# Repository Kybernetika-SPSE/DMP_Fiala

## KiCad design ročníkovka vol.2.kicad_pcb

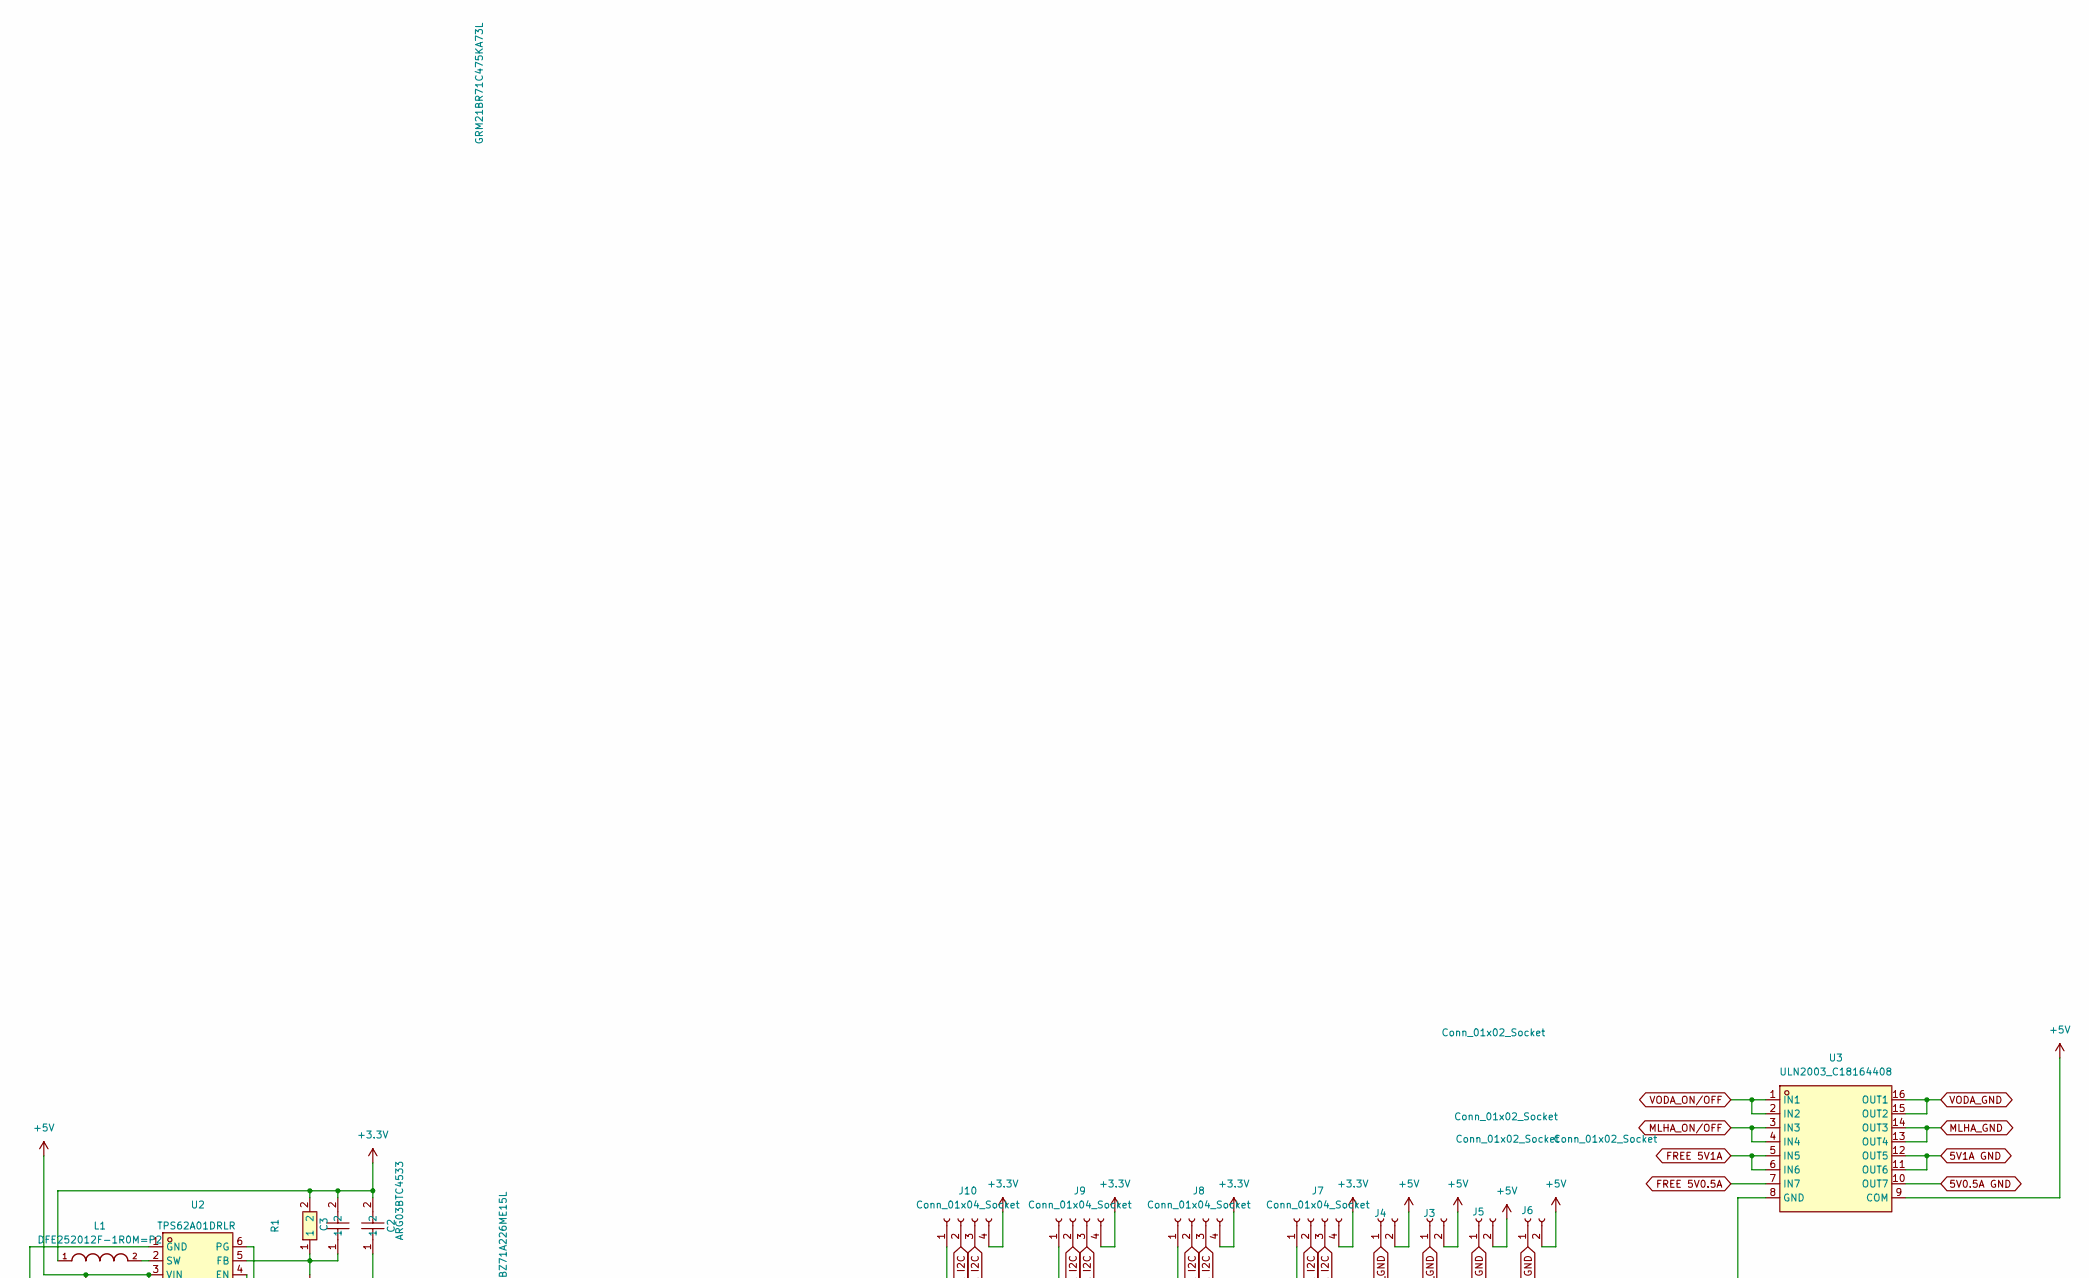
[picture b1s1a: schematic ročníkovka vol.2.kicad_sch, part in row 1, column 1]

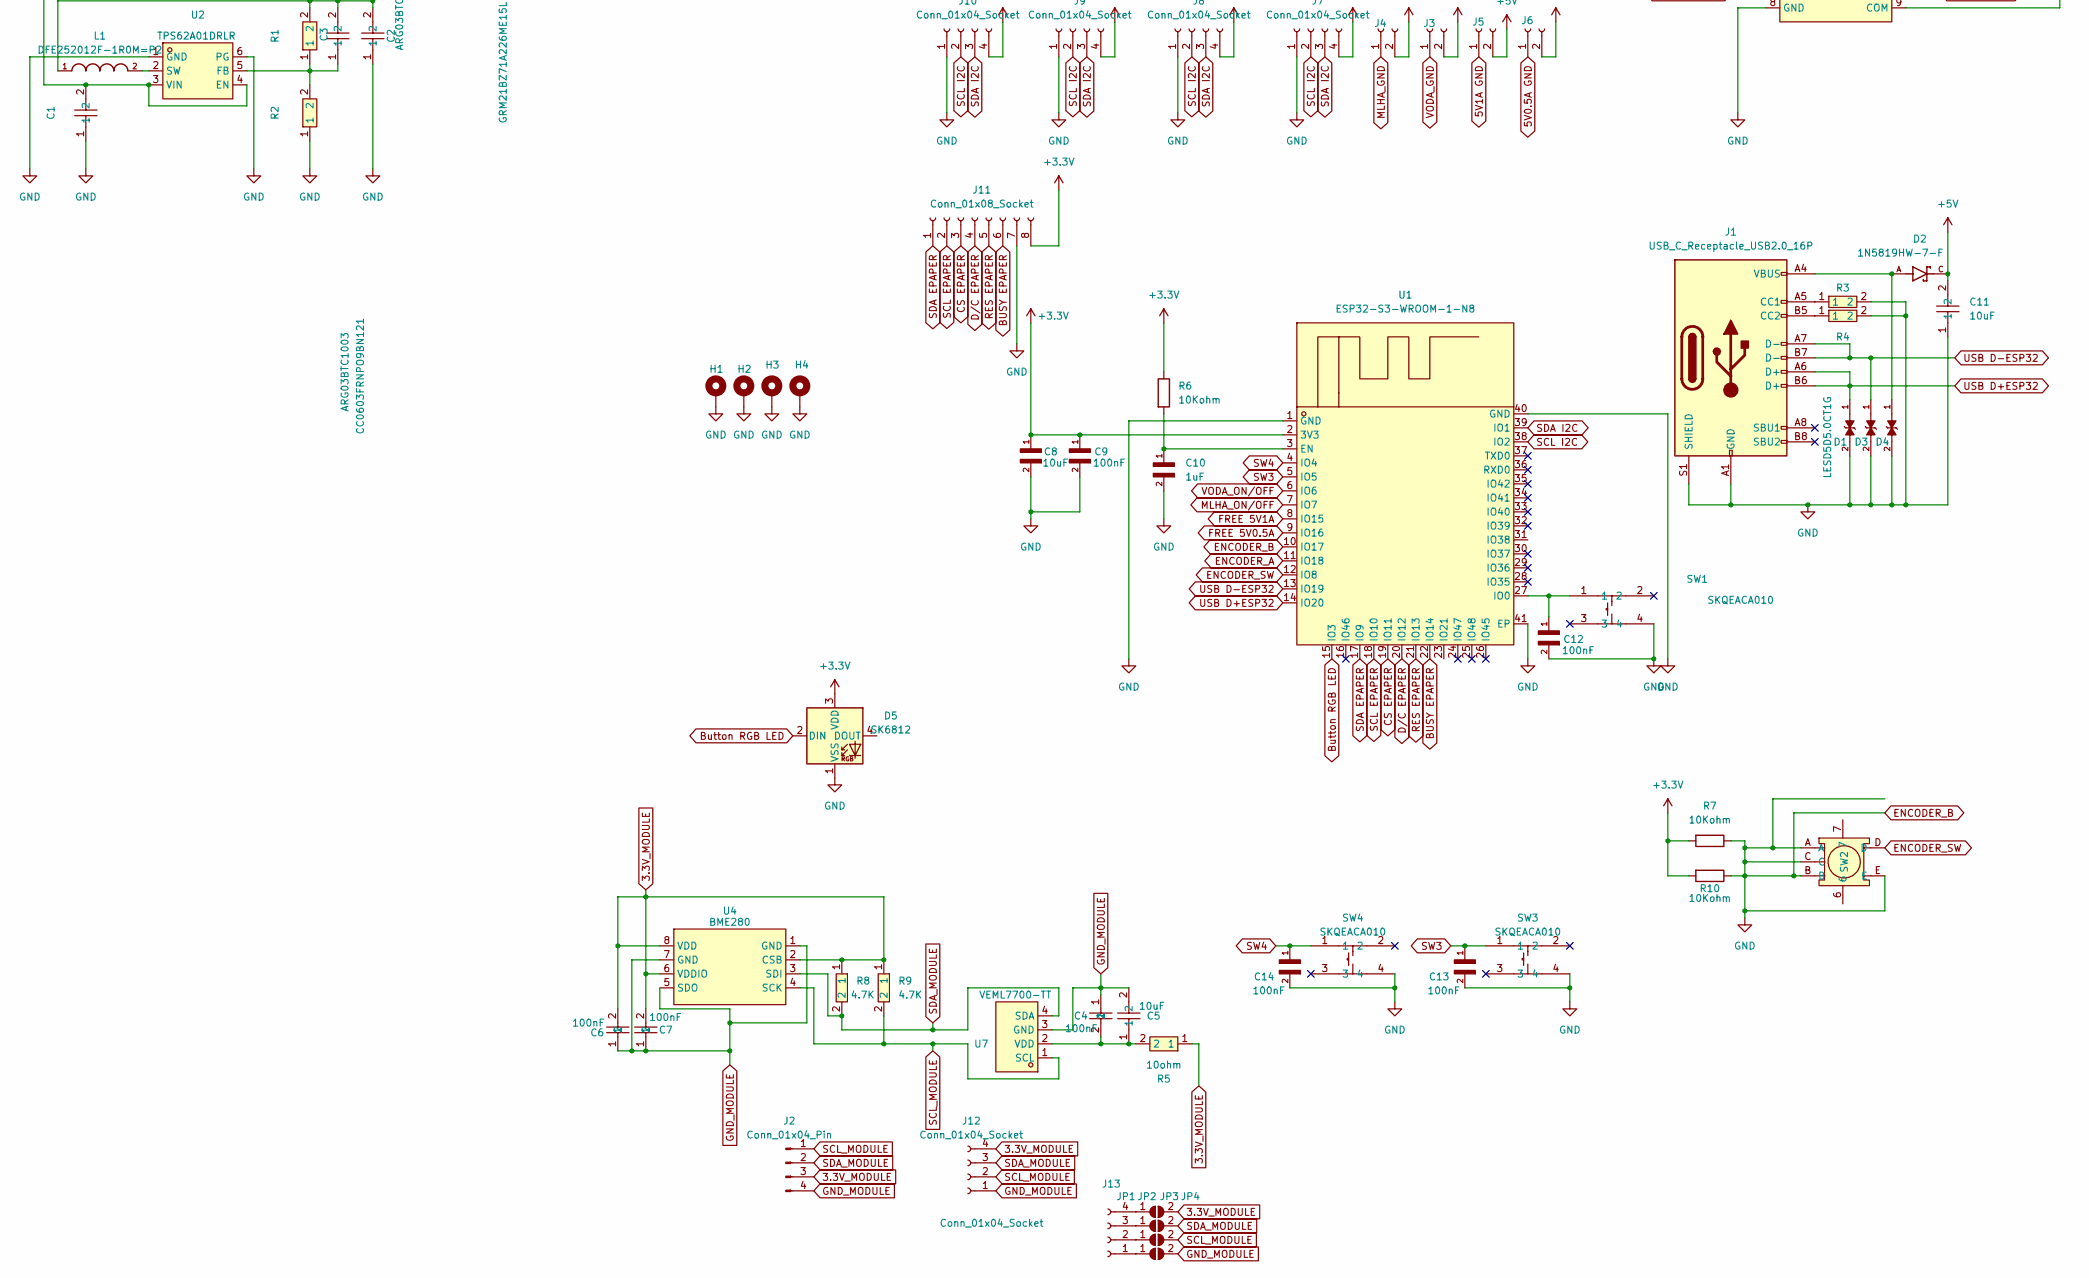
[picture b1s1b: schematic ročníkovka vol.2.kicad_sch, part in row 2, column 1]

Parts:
C1: GRM21BR71C475KA73L; C0805; LCSC Part C86040
C2: GRM21BZ71A226ME15L; C0805; LCSC Part C907991
C3: CC0603FRNPO9BN121; C0603; LCSC Part C519498
C4, C6, C7: 100nF; C0603; LCSC Part C24452
C5: 10uF; C0603; LCSC Part C962136
C8: 10uF; CAPC1608X90N
C9, C12, C13, C14: 100nF; CAPC1608X90N
C10: 1uF; CAPC1608X90N
C11: 10uF; C0603; LCSC Part C96446
D1, D3, D4: LESD5D5.0CT1G; TVS_LESD5D5.0CT1G; PARTREV O
D2: 1N5819HW-7-F; SOD3715X145N; PARTREV 18-2
D5: SK6812; LED_SK6812_PLCC4_5.0x5.0mm_P3.2mm
H1, H2, H3, H4: MountingHole_Pad; MountingHole_3.2mm_M3_Pad_TopBottom
J1: USB_C_Receptacle_USB2.0_16P; USB_C_Receptacle_GCT_USB4105-xx-A_16P_TopMnt_Horizontal; LCSC Part C2988369
J2: Conn_01x04_Pin; JST_PH_B4B-PH-K_1x04_P2.00mm_Vertical
J3, J4, J5, J6: Conn_01x02_Socket; JST_PH_S2B-PH-K_1x02_P2.00mm_Horizontal
J7, J8, J9, J10, J12, J13: Conn_01x04_Socket; JST_PH_S4B-PH-K_1x04_P2.00mm_Horizontal
J11: Conn_01x08_Socket; JST_PH_S8B-PH-K_1x08_P2.00mm_Horizontal
JP1, JP2, JP3, JP4: SolderJumper_2_Open; SolderJumper-2_P1.3mm_Open_TrianglePad1.0x1.5mm
L1: DFE252012F-1R0M=P2; INDC2520X120N
R1: ARG03BTC4533; R0603; LCSC Part C2686428
R2: ARG03BTC1003; R0603; LCSC Part C335088
R3, R4: 0603WAF5101T5E; R0603; LCSC Part C23186
R5: 10ohm; R0603; LCSC Part C414987
R6, R7, R10: 10Kohm; RESC1608X55N
R8, R9: 4.7K; R0603; LCSC Part C99782
SW1, SW3, SW4: SKQEACA010; KEY-TH_4P-L12.0-W12.0-P5.0-LS12.5-EH; LCSC Part C107236
SW2: EC11E15244G1; SW-TH_EC11E15244G1; LCSC Part C370970
U1: ESP32-S3-WROOM-1-N8; WIFIM-SMD_ESP32-S3-WROOM-1-N8; LCSC Part C2913198
U2: TPS62A01DRLR; SOT-5X3-6_L1.6-W1.2-P0.50-LS1.6-BR; LCSC Part C5157937
U3: ULN2003_C18164408; SOP-16_L9.9-W3.9-P1.27-LS6.0-BL; LCSC Part C18164408
U4: BME280; PSON65P250X250X100-8N; LCSC Part C92489
U7: VEML7700-TT; SENSOR-SMD_EML7700-TT; LCSC Part C1850416

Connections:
3.3V_MODULE: C6.2, C7.2, J2.3, J12.4, JP1.2 (B), R5.1, R8.1, R9.1, U4.2 (CSB), U4.6 (VDDIO), U4.8 (VDD)
5V0.5A GND: J6.1, U3.10 (OUT7)
5V1A GND: J5.1, U3.11 (OUT6), U3.12 (OUT5)
+3.3V: C2.2, C3.2, C8.1, C9.1, D5.3 (VDD), J7.4, J8.4, J9.4, J10.4, J11.8, L1.1, R1.2, R6.1, R7.2, R10.2, U1.2 (3V3)
+5V: C1.2, C11.2, D2.C, J3.2, J4.2, J5.2, J6.2, U2.3 (VIN), U2.4 (EN), U3.9 (COM)
BUSY EPAPER: J11.6, U1.22 (IO14)
Button RGB LED: D5.2 (DIN), U1.15 (IO3)
CS EPAPER: J11.3, U1.19 (IO11)
D/C EPAPER: J11.4, U1.20 (IO12)
ENCODER_A: U1.11 (IO18)
ENCODER_B: C1.1, C2.1, C8.2, C9.2, C10.2, C11.1, C12.2, C13.2, C14.2, D1.2, D3.2, D4.2, D5.1 (VSS), H1.1, H2.1, H3.1, H4.1, J1.A1 (GND), J1.A12 (GND), J1.B1 (GND), J1.B12 (GND), J1.S1 (SHIELD), J7.1, J8.1, J9.1, J10.1, J11.7, R2.1, R3.2, R4.2, R7.1, R10.1, SW1.4, SW2.A, SW2.B, SW2.C, SW2.E, SW3.4, SW4.4, U1.1 (GND), U1.10 (IO17), U1.40 (GND), U1.41 (EP), U2.1 (GND), U2.6 (PG), U3.8 (GND)
ENCODER_SW: SW2.D, U1.12 (IO8)
FREE 5V0.5A: U1.9 (IO16), U3.7 (IN7)
FREE 5V1A: U1.8 (IO15), U3.5 (IN5), U3.6 (IN6)
GND_MODULE: C4.1, C5.2, C6.1, C7.1, J2.4, J12.1, JP4.2 (B), U4.1 (GND), U4.5 (SDO), U4.7 (GND), U7.3 (GND)
MLHA_GND: J4.1, U3.13 (OUT4), U3.14 (OUT3)
MLHA_ON/OFF: U1.7 (IO7), U3.3 (IN3), U3.4 (IN4)
unnamed: D2.A, D4.1, J1.A4 (VBUS), J1.A9 (VBUS), J1.B4 (VBUS), J1.B9 (VBUS)
unnamed: J1.A5 (CC1), R3.1
unnamed: J1.B5 (CC2), R4.1
unnamed: J13.1, JP4.1 (A)
unnamed: J13.2, JP3.1 (A)
unnamed: J13.3, JP2.1 (A)
unnamed: J13.4, JP1.1 (A)
unnamed: C10.1, R6.2, U1.3 (EN)
unnamed: C12.1, SW1.1, U1.27 (IO0)
unnamed: C3.1, R1.1, R2.2, U2.5 (FB)
unnamed: L1.2, U2.2 (SW)
unnamed: C4.2, C5.1, R5.2, U7.2 (VDD)
RES EPAPER: J11.5, U1.21 (IO13)
SCL EPAPER: J11.2, U1.18 (IO10)
SCL I2C: J7.2, J8.2, J9.2, J10.2, U1.38 (IO2)
SCL_MODULE: J2.1, J12.2, JP3.2 (B), R9.2, U4.4 (SCK), U7.1 (SCL)
SDA EPAPER: J11.1, U1.17 (IO9)
SDA I2C: J7.3, J8.3, J9.3, J10.3, U1.39 (IO1)
SDA_MODULE: J2.2, J12.3, JP2.2 (B), R8.2, U4.3 (SDI), U7.4 (SDA)
SW3: C13.1, SW3.1, U1.5 (IO5)
SW4: C14.1, SW4.1, U1.4 (IO4)
USB D+ESP32: D1.1, J1.A6 (D+), J1.B6 (D+), U1.14 (IO20)
USB D-ESP32: D3.1, J1.A7 (D-), J1.B7 (D-), U1.13 (IO19)
VODA_GND: J3.1, U3.15 (OUT2), U3.16 (OUT1)
VODA_ON/OFF: U1.6 (IO6), U3.1 (IN1), U3.2 (IN2)

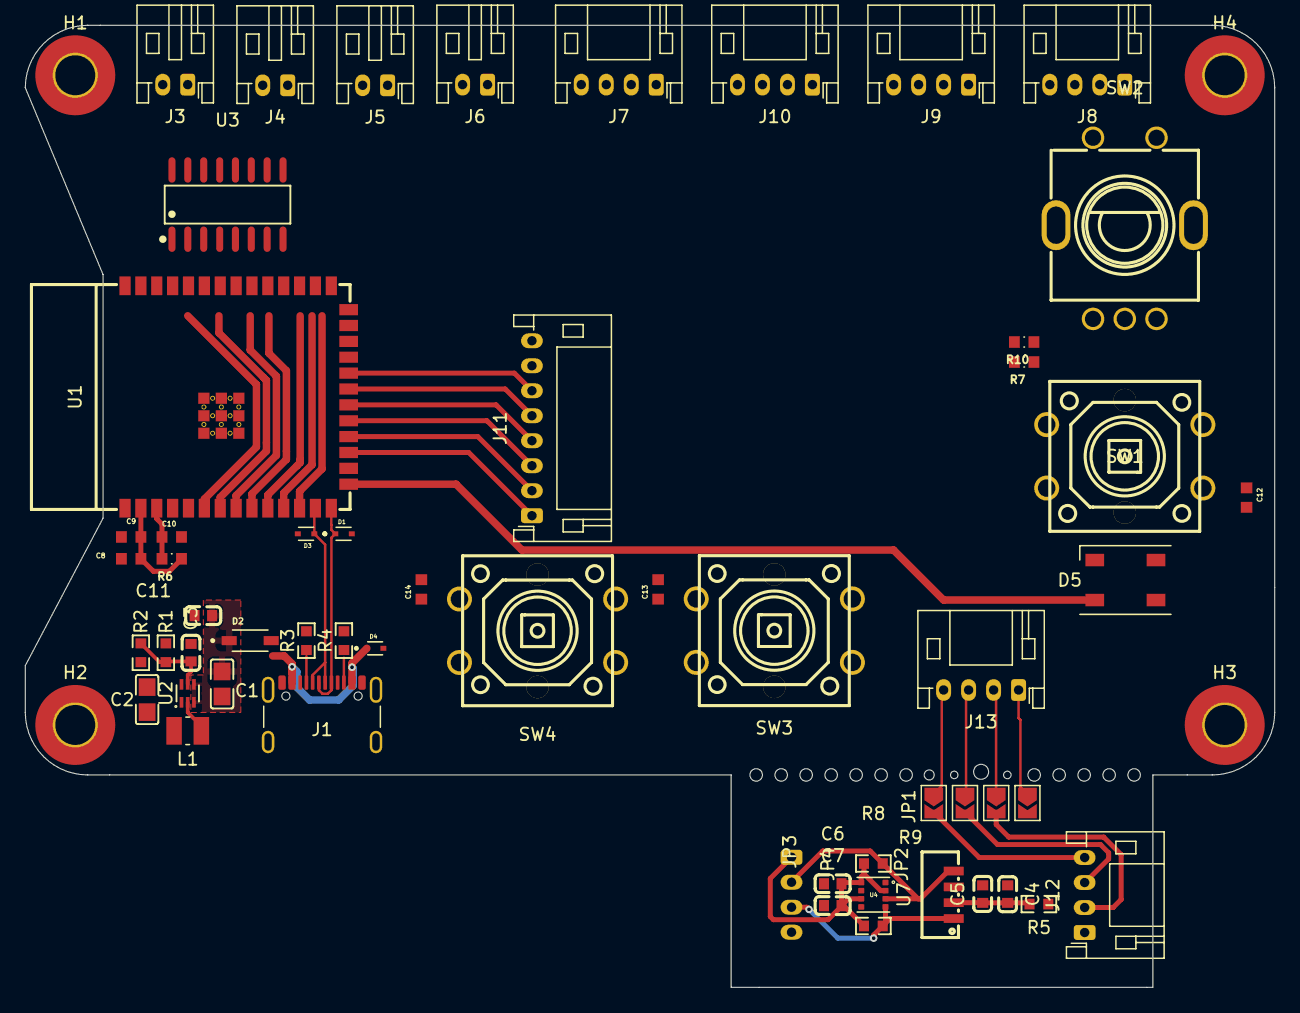
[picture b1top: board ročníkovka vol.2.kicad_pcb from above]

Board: 2 copper layers, 100.0 x 77.0 mm, 60 parts (1 on the bottom side), 41 nets.

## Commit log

2024-10-31 dílčí vypracování říjen 31.10. 2024 Fiala
2025-01-09 přidány soubory KICAD projektu
